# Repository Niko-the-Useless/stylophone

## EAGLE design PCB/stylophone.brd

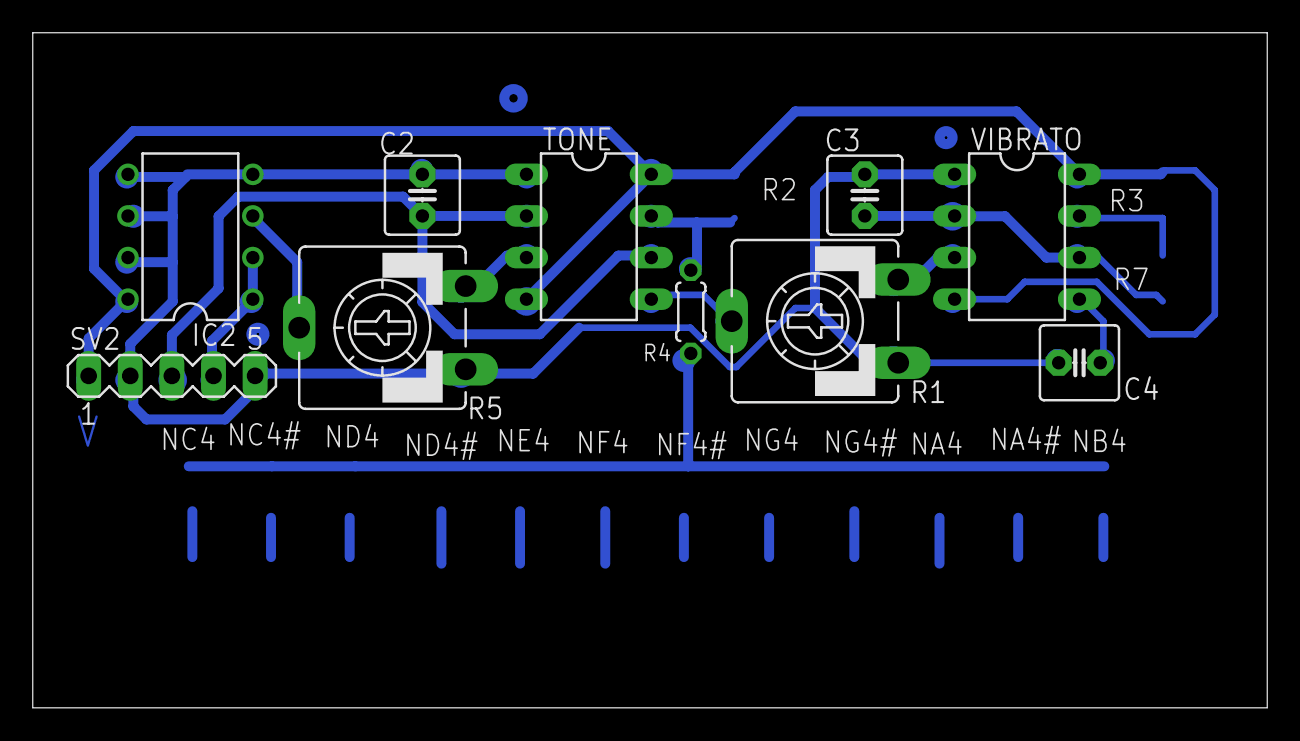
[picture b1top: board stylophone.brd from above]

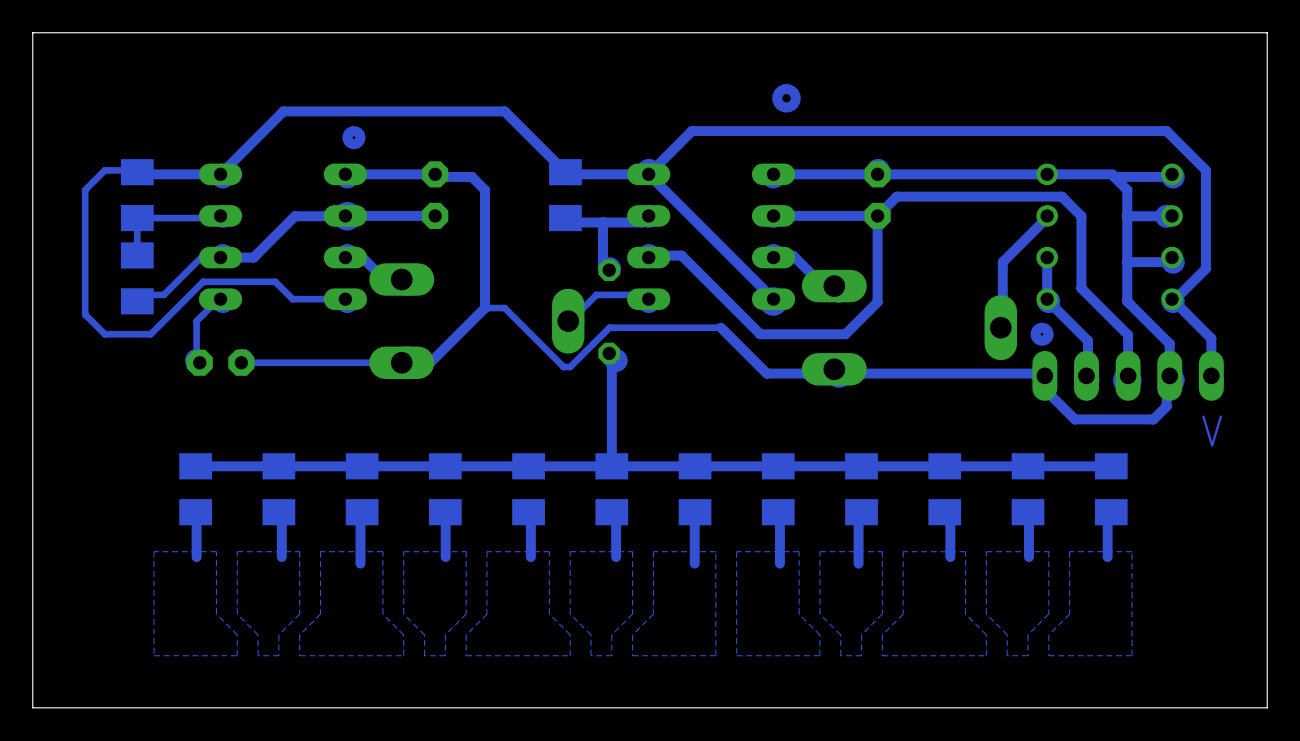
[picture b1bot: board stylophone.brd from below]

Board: 2 copper layers, 75.3 x 41.2 mm, 25 parts (15 on the bottom side), 13 nets.

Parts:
C2: 100n; C2.5-5
C3: 1u; C2.5-5
C4: 10n; C2.5-5
IC2: LM358N; DIL08
NA4, NA4#: M1206
NB4: M1206
NC4, NC4#: M1206
ND4, ND4#: M1206
NE4: M1206
NF4, NF4#: M1206
NG4, NG4#: M1206
R1, R5: CA9V
R2: 1k; M1206
R3: 150k; M1206
R4: 0204/5
R7: 10k; M1206
SV2: MA05-1
TONE: NE555; DIL-08
VIBRATO: NE555; DIL-08

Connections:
GND: C2.2, C3.2, C4.2, IC2.4, R1.A, R5.A, SV2.2, SV2.5, TONE.1, VIBRATO.1
KEYBOARD: NA4.2, NA4#.2, NB4.2, NC4.2, NC4#.2, ND4.2, ND4#.2, NE4.2, NF4.2, NF4#.2, NG4.2, NG4#.2, R4.2
unnamed: C4.1, VIBRATO.5
unnamed: R1.E, VIBRATO.3
unnamed: R3.2, R7.1, VIBRATO.7
unnamed: IC2.3, R5.S
NOTE: R2.2, R4.1, TONE.7
NOTSTYLUS: C3.1, R7.2, VIBRATO.2, VIBRATO.6
OUTPUT: IC2.1, IC2.2, SV2.4
STYLUS: C2.1, SV2.3, TONE.2, TONE.6
TONE: R5.E, TONE.3
VCC: IC2.8, R2.1, R3.1, SV2.1, TONE.4, TONE.8, VIBRATO.4, VIBRATO.8
VIBRATO: R1.S, TONE.5

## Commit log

2025-10-20 spice sim
2025-11-04 PCB ver1
2025-11-04 fixed project structure
2025-11-04 vibrato freq
2025-11-05 almost finished
2025-11-05 almost done
2025-11-05 pots
2025-11-06 bottom
2025-11-07 images
2025-11-07 sprawko
2025-11-07 repo cleaning
2025-11-07 done
2025-11-07 formating
2025-11-07 finished fr
2025-11-07 frfr
